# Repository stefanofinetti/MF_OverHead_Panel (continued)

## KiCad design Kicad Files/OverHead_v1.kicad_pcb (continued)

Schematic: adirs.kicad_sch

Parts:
H21, H22, H23, H24: MountingHole; MountingHole_3.2mm_M3_DIN965_Pad_TopBottom
SW24: GND_CTL; G-Switch PS-7054DVB-6PN
SW25: ADR_1; Rotary_SW_8x1
SW26: ADR_2; Rotary_SW_8x1
SW27: ADR_3; Rotary_SW_8x1

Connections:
ADR_1_ATT: SW25.3; also elsewhere on the board
ADR_1_NAV: SW25.2; also elsewhere on the board
ADR_1_OFF: SW25.1; also elsewhere on the board
ADR_2_ATT: SW26.3; also elsewhere on the board
ADR_2_NAV: SW26.2; also elsewhere on the board
ADR_2_OFF: SW26.1; also elsewhere on the board
ADR_3_ATT: SW27.3; also elsewhere on the board
ADR_3_NAV: SW27.2; also elsewhere on the board
ADR_3_OFF: SW27.1; also elsewhere on the board
GND: SW24.2, SW25.9, SW26.9, SW27.9; also elsewhere on the board
GND_CTL_SW: SW24.1; also elsewhere on the board

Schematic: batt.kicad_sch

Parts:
H30, H31, H32, H33: MountingHole; MountingHole_3.2mm_M3_DIN965_Pad_TopBottom
SW14: OXY_CREW_SUPPLY; G-Switch PS-7054DVB-6PN
SW15: ELEC_BATT_1; G-Switch PS-7054DVB-6PN
SW16: ELEC_BATT_2; G-Switch PS-7054DVB-6PN

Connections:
ELEC_BATT_1_SW: SW15.1; also elsewhere on the board
ELEC_BATT_2_SW: SW16.1; also elsewhere on the board
GND: SW14.2, SW15.2, SW16.2; also elsewhere on the board
OXY_CREW_SUPPLY_SW: SW14.1; also elsewhere on the board

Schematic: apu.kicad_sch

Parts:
H1, H2, H3, H4: MountingHole; MountingHole_3.2mm_M3_DIN965_Pad_TopBottom
SW1: APU_MASTER_SW; G-Switch PS-7054DVB-6PN
SW2: APU_START_SW; G-Switch PS-7054DVB-6PN

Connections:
APU_MASTER_SW: SW1.1; also elsewhere on the board
APU_START_SW: SW2.1; also elsewhere on the board
GND: SW1.2, SW2.2; also elsewhere on the board

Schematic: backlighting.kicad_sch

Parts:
D5, D6, D7, D8, D9, D10, D11, D12, D13, D14, D15, D16, D17, D18, D19, D20, D21, D22, D23, D24, D25, D26, D27, D28, D29, D30, D31, D32, D33, D34, D35, D36, D37, D38, D39, D40, D41, D42, D43, D44, D45, D46, D47, D48, D49, D53, D54, D55, D56, D57, D58, D59, D60, D61, D62, D63, D64, D65, D66, D67, D68, D69, D70, D71, D72, D73, D74, D81, D82, D83, D84, D85, D86, D88, D93, D94, D95, D96, D97, D98, D100, D101, D102, D104, D105, D110, D111, D112, D113, D114, D115, D116, D117, D118, D119, D134, D135, D136, D137, D138, D139, D140, D141, D142, D143, D144, D146, D147, D148, D149, D150, D151, D152, D153, D154, D155, D156, D157, D158, D159, D160, D161: LED; LED_1206_3216Metric_Pad1.42x1.75mm_HandSolder
R9, R10, R11, R12, R13, R14, R15, R16, R17, R18, R19, R20, R21, R22, R23, R24, R25, R26, R27, R28, R29, R30, R31, R32, R33, R34, R35, R36, R37, R38, R39, R40, R57, R58, R59, R60, R61, R62, R63, R64, R65, R66, R67, R68, R69, R70, R71, R72, R73, R74, R75, R76, R77, R78, R79, R80, R81, R82, R83, R84, R85: 150; R_1206_3216Metric_Pad1.30x1.75mm_HandSolder

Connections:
+9V: D5.2 (A), D7.2 (A), D9.2 (A), D11.2 (A), D13.2 (A), D15.2 (A), D17.2 (A), D19.2 (A), D21.2 (A), D23.2 (A), D25.2 (A), D27.2 (A), D29.2 (A), D31.2 (A), D33.2 (A), D35.2 (A), D37.2 (A), D39.2 (A), D41.2 (A), D43.2 (A), D45.2 (A), D47.2 (A), D49.2 (A), D54.2 (A), D56.2 (A), D58.2 (A), D60.2 (A), D62.2 (A), D64.2 (A), D66.2 (A), D68.2 (A), D70.2 (A), D72.2 (A), D74.2 (A), D82.2 (A), D84.2 (A), D86.2 (A), D93.2 (A), D95.2 (A), D97.2 (A), D100.2 (A), D102.2 (A), D105.2 (A), D111.2 (A), D113.2 (A), D115.2 (A), D117.2 (A), D119.2 (A), D135.2 (A), D137.2 (A), D139.2 (A), D141.2 (A), D143.2 (A), D146.2 (A), D148.2 (A), D150.2 (A), D152.2 (A), D154.2 (A), D156.2 (A), D158.2 (A), D160.2 (A); also elsewhere on the board
GND: R9.2, R10.2, R11.2, R12.2, R13.2, R14.2, R15.2, R16.2, R17.2, R18.2, R19.2, R20.2, R21.2, R22.2, R23.2, R24.2, R25.2, R26.2, R27.2, R28.2, R29.2, R30.2, R31.2, R32.2, R33.2, R34.2, R35.2, R36.2, R37.2, R38.2, R39.2, R40.2, R57.2, R58.2, R59.2, R60.2, R61.2, R62.2, R63.2, R64.2, R65.2, R66.2, R67.2, R68.2, R69.2, R70.2, R71.2, R72.2, R73.2, R74.2, R75.2, R76.2, R77.2, R78.2, R79.2, R80.2, R81.2, R82.2, R83.2, R84.2, R85.2; also elsewhere on the board
unnamed: D5.1 (K), D6.2 (A)
unnamed: D6.1 (K), R9.1
unnamed: D7.1 (K), D8.2 (A)
unnamed: D8.1 (K), R10.1
unnamed: D9.1 (K), D10.2 (A)
unnamed: D10.1 (K), R11.1
unnamed: D11.1 (K), D12.2 (A)
unnamed: D12.1 (K), R12.1
unnamed: D13.1 (K), D14.2 (A)
unnamed: D14.1 (K), R13.1
unnamed: D15.1 (K), D16.2 (A)
unnamed: D16.1 (K), R14.1
unnamed: D17.1 (K), D18.2 (A)
unnamed: D18.1 (K), R15.1
unnamed: D19.1 (K), D20.2 (A)
unnamed: D20.1 (K), R16.1
unnamed: D21.1 (K), D22.2 (A)
unnamed: D22.1 (K), R17.1
unnamed: D23.1 (K), D24.2 (A)
unnamed: D24.1 (K), R18.1
unnamed: D25.1 (K), D26.2 (A)
unnamed: D26.1 (K), R19.1
unnamed: D27.1 (K), D28.2 (A)
unnamed: D28.1 (K), R20.1
unnamed: D29.1 (K), D30.2 (A)
unnamed: D30.1 (K), R21.1
unnamed: D31.1 (K), D32.2 (A)
unnamed: D32.1 (K), R22.1
unnamed: D33.1 (K), D34.2 (A)
unnamed: D34.1 (K), R23.1
unnamed: D35.1 (K), D36.2 (A)
unnamed: D36.1 (K), R24.1
unnamed: D37.1 (K), D38.2 (A)
unnamed: D38.1 (K), R25.1
unnamed: D39.1 (K), D40.2 (A)
unnamed: D40.1 (K), R26.1
unnamed: D41.1 (K), D42.2 (A)
unnamed: D42.1 (K), R27.1
unnamed: D43.1 (K), D44.2 (A)
unnamed: D44.1 (K), R28.1
unnamed: D45.1 (K), D46.2 (A)
unnamed: D46.1 (K), R29.1
unnamed: D47.1 (K), D48.2 (A)
unnamed: D48.1 (K), R30.1
unnamed: D49.1 (K), D53.2 (A)
unnamed: D53.1 (K), R31.1
unnamed: D54.1 (K), D55.2 (A)
unnamed: D55.1 (K), R32.1
unnamed: D56.1 (K), D57.2 (A)
unnamed: D57.1 (K), R33.1
unnamed: D58.1 (K), D59.2 (A)
unnamed: D59.1 (K), R34.1
unnamed: D60.1 (K), D61.2 (A)
unnamed: D61.1 (K), R35.1
unnamed: D62.1 (K), D63.2 (A)
unnamed: D63.1 (K), R36.1
unnamed: D64.1 (K), D65.2 (A)
unnamed: D65.1 (K), R37.1
unnamed: D66.1 (K), D67.2 (A)
unnamed: D67.1 (K), R38.1
unnamed: D68.1 (K), D69.2 (A)
unnamed: D69.1 (K), R39.1
unnamed: D70.1 (K), D71.2 (A)
unnamed: D71.1 (K), R40.1
unnamed: D72.1 (K), D73.2 (A)
unnamed: D73.1 (K), R57.1
unnamed: D74.1 (K), D81.2 (A)
unnamed: D81.1 (K), R58.1
unnamed: D82.1 (K), D83.2 (A)
unnamed: D83.1 (K), R59.1
unnamed: D84.1 (K), D85.2 (A)
unnamed: D85.1 (K), R60.1
unnamed: D86.1 (K), D88.2 (A)
unnamed: D88.1 (K), R61.1
unnamed: D93.1 (K), D94.2 (A)
unnamed: D94.1 (K), R62.1
unnamed: D95.1 (K), D96.2 (A)
unnamed: D96.1 (K), R63.1
unnamed: D97.1 (K), D98.2 (A)
unnamed: D98.1 (K), R64.1
unnamed: D100.1 (K), D101.2 (A)
unnamed: D101.1 (K), R65.1
unnamed: D102.1 (K), D104.2 (A)
unnamed: D104.1 (K), R66.1
unnamed: D105.1 (K), D110.2 (A)
unnamed: D110.1 (K), R67.1
unnamed: D111.1 (K), D112.2 (A)
unnamed: D112.1 (K), R68.1
unnamed: D113.1 (K), D114.2 (A)
unnamed: D114.1 (K), R69.1
unnamed: D115.1 (K), D116.2 (A)
unnamed: D116.1 (K), R70.1
unnamed: D117.1 (K), D118.2 (A)
unnamed: D118.1 (K), R71.1
unnamed: D119.1 (K), D134.2 (A)
unnamed: D134.1 (K), R72.1
unnamed: D135.1 (K), D136.2 (A)
unnamed: D136.1 (K), R73.1
unnamed: D137.1 (K), D138.2 (A)
unnamed: D138.1 (K), R74.1
unnamed: D139.1 (K), D140.2 (A)
unnamed: D140.1 (K), R75.1
unnamed: D141.1 (K), D142.2 (A)
unnamed: D142.1 (K), R76.1
unnamed: D143.1 (K), D144.2 (A)
unnamed: D144.1 (K), R77.1
unnamed: D146.1 (K), D147.2 (A)
unnamed: D147.1 (K), R78.1
unnamed: D148.1 (K), D149.2 (A)
unnamed: D149.1 (K), R79.1
unnamed: D150.1 (K), D151.2 (A)
unnamed: D151.1 (K), R80.1
unnamed: D152.1 (K), D153.2 (A)
unnamed: D153.1 (K), R81.1
unnamed: D154.1 (K), D155.2 (A)
unnamed: D155.1 (K), R82.1
unnamed: D156.1 (K), D157.2 (A)
unnamed: D157.1 (K), R83.1
unnamed: D158.1 (K), D159.2 (A)
unnamed: D159.1 (K), R84.1
unnamed: D160.1 (K), D161.2 (A)
unnamed: D161.1 (K), R85.1

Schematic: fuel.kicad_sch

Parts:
H25, H26, H27, H28, H29: MountingHole; MountingHole_3.2mm_M3_DIN965_Pad_TopBottom
SW17: LT_TK_PUMP_1; G-Switch PS-7054DVB-6PN
SW18: LT_TK_PUMP_2; G-Switch PS-7054DVB-6PN
SW19: L_XFER; G-Switch PS-7054DVB-6PN
SW20: X_FEED; G-Switch PS-7054DVB-6PN
SW21: R_XFER; G-Switch PS-7054DVB-6PN
SW22: RT_TK_PUMP_1; G-Switch PS-7054DVB-6PN
SW23: RT_TK_PUMP_2; G-Switch PS-7054DVB-6PN

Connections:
CTR_TK_PUMP_1_SW: SW19.1; also elsewhere on the board
CTR_TK_PUMP_2_SW: SW21.1; also elsewhere on the board
GND: SW17.2, SW18.2, SW19.2, SW20.2, SW21.2, SW22.2, SW23.2; also elsewhere on the board
LT_TK_PUMP_1_SW: SW17.1; also elsewhere on the board
LT_TK_PUMP_2_SW: SW18.1; also elsewhere on the board
RT_TK_PUMP_1_SW: SW22.1; also elsewhere on the board
RT_TK_PUMP_2_SW: SW23.1; also elsewhere on the board
XFEED_SW: SW20.1; also elsewhere on the board

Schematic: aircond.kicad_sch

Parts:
H17, H18, H19, H20: MountingHole; MountingHole_3.2mm_M3_DIN965_Pad_TopBottom
SW10: APU BLEED; G-Switch PS-7054DVB-6PN
SW11: PACK1; G-Switch PS-7054DVB-6PN
SW12: PACK2; G-Switch PS-7054DVB-6PN
SW13: EXT_PWR; G-Switch PS-7054DVB-6PN

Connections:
APU_BLEED_SW: SW10.1; also elsewhere on the board
EXT_PWR_SW: SW13.1; also elsewhere on the board
GND: SW10.2, SW11.2, SW12.2, SW13.2; also elsewhere on the board
PACK1_SW: SW11.1; also elsewhere on the board
PACK2_SW: SW12.1; also elsewhere on the board

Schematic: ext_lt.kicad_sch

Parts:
H5, H6, H7, H8: MountingHole; MountingHole_3.2mm_M3_DIN965_Pad_TopBottom
S1: LDG_LIGHT_L; Toggle_Switch_100SP1T1B4M2QE; MPN 100SP1T1B4M2QE; Digi-Key_PN EG2355-ND
S2: LDG_LIGHT_R; Toggle_Switch_100SP1T1B4M2QE; MPN 100SP1T1B4M2QE; Digi-Key_PN EG2355-ND
S3: NOSE_LIGHT; Toggle_Switch_100SP1T1B4M2QE; MPN 100SP1T1B4M2QE; Digi-Key_PN EG2355-ND
S4: NAV&LOGO; Toggle_Switch_100SP1T1B4M2QE; MPN 100SP1T1B4M2QE; Digi-Key_PN EG2355-ND
S5: WING; Toggle_Switch_100SP1T1B4M2QE; MPN 100SP1T1B4M2QE; Digi-Key_PN EG2355-ND
S6: BEACON; Toggle_Switch_100SP1T1B4M2QE; MPN 100SP1T1B4M2QE; Digi-Key_PN EG2355-ND
S7: STROBE; Toggle_Switch_100SP1T1B4M2QE; MPN 100SP1T1B4M2QE; Digi-Key_PN EG2355-ND
S8: RWY TURN; Toggle_Switch_100SP1T1B4M2QE; MPN 100SP1T1B4M2QE; Digi-Key_PN EG2355-ND

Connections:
BEACON_ON: S6.1; also elsewhere on the board
GND: S1.2 (Com), S2.2 (Com), S3.2 (Com), S4.2 (Com), S5.2 (Com), S6.2 (Com), S7.2 (Com), S8.2 (Com); also elsewhere on the board
L_LDG_LIGHT_ON: S1.1; also elsewhere on the board
L_LDG_LIGHT_RETR: S1.3; also elsewhere on the board
NAV_1: S4.1; also elsewhere on the board
NAV_1_OFF: S4.3; also elsewhere on the board
NOSE_OFF: S3.3; also elsewhere on the board
NOSE_TO: S3.1; also elsewhere on the board
RWY_TURN_ON: S8.1; also elsewhere on the board
R_LDG_LIGHT_ON: S2.1; also elsewhere on the board
R_LDG_LIGHT_RETR: S2.3; also elsewhere on the board
STROBE_ON: S7.1; also elsewhere on the board
WING_ON: S5.1; also elsewhere on the board

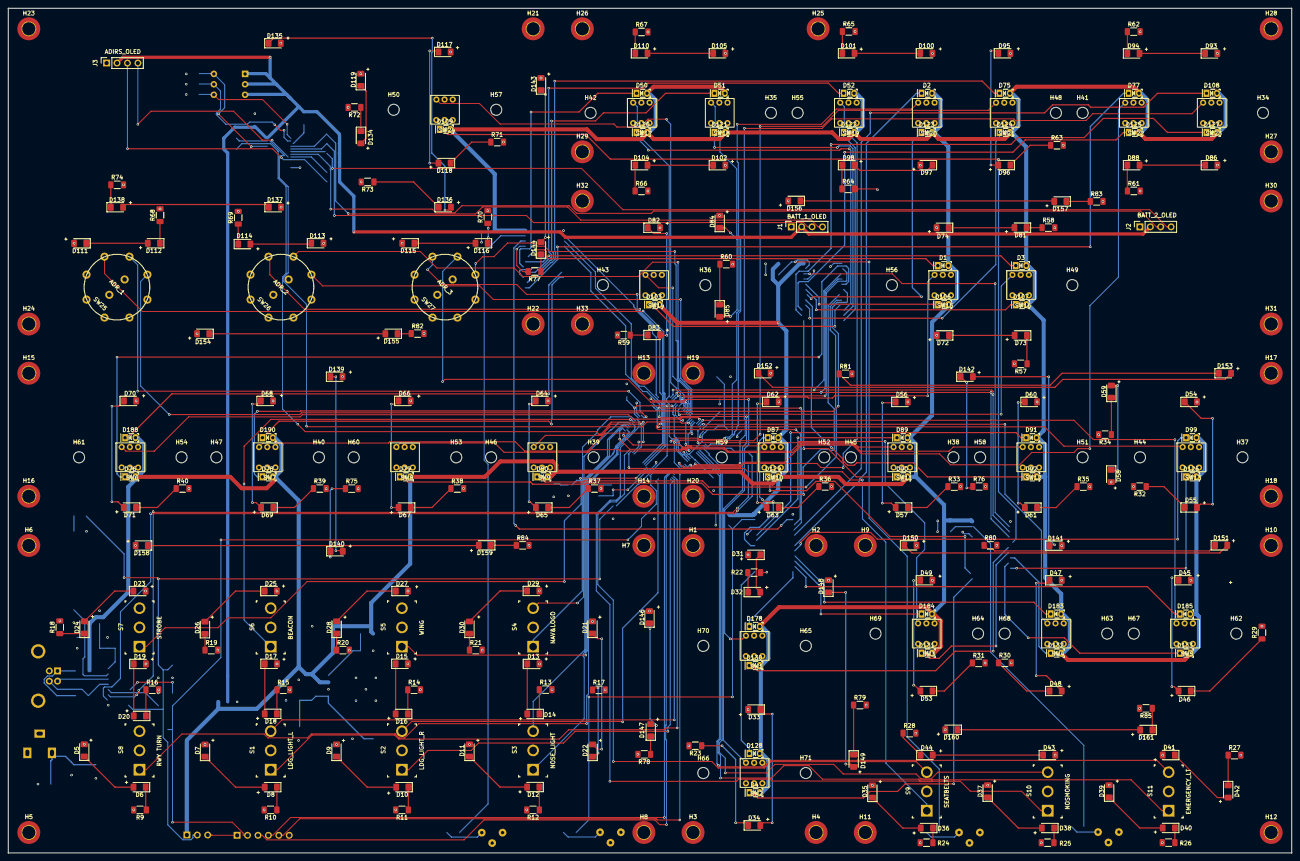
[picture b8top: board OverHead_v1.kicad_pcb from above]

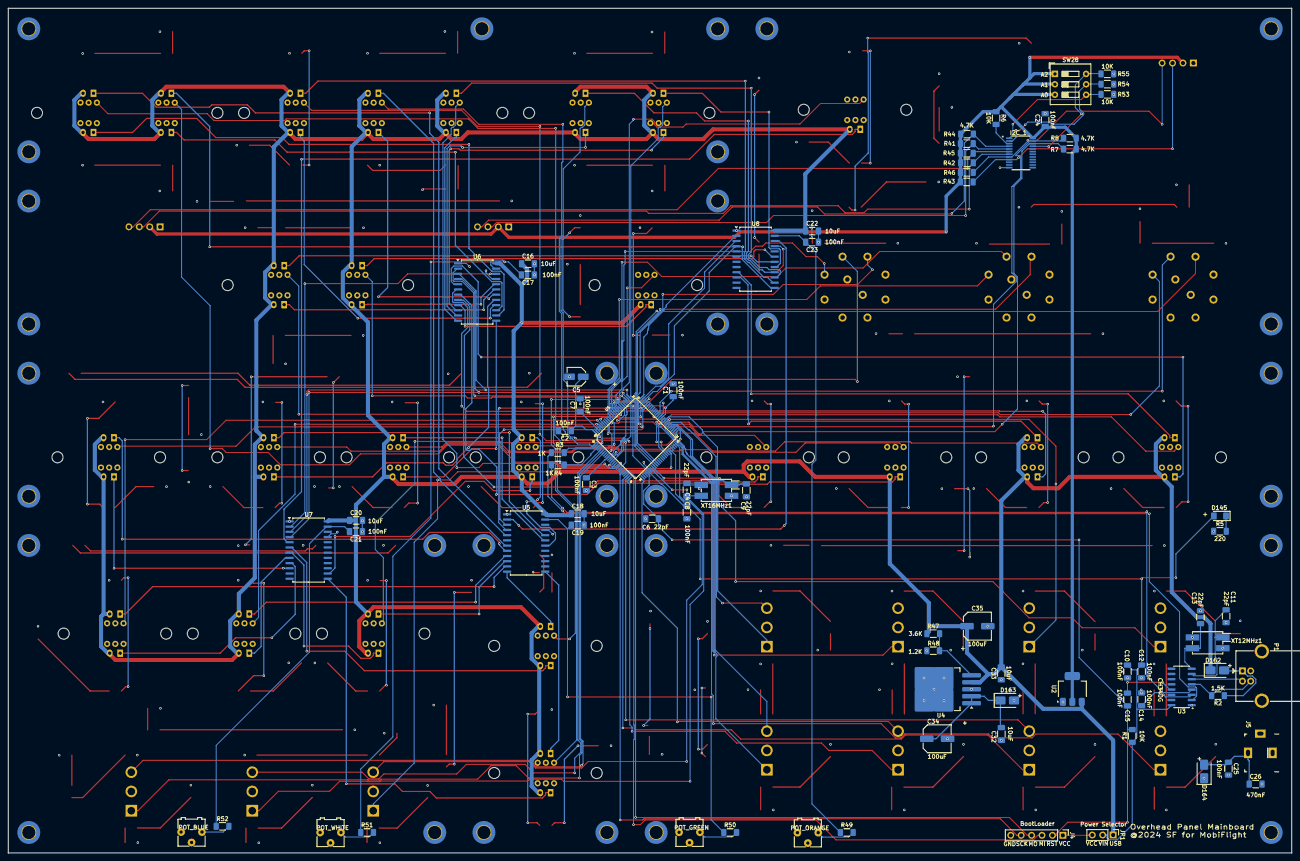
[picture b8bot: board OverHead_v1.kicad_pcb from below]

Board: 4 copper layers, 313.0 x 206.0 mm, 416 parts (77 on the bottom side), 271 nets.

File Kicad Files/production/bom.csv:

Designator,Footprint,Quantity,Value,LCSC Part #
"C1, C10, C12, C14, C15, C17, C19, C2, C21, C23, C24, C25, C3, C4, C7",1206,15,100nF,
"C11, C13, C6, C8, C9",1206,5,22pF,
"C16, C18, C20, C22, C32, C33",1206,6,10uF,
C26,1206,1,470nF,
"C34, C35",C_Elec_6.3x7.7,2,100uF,
C5,C_Elec_4x5.4,1,10uF,
"D1, D120, D121, D122, D123, D124, D125, D127, D129, D130, D131, D183, D185, D3, D4, D76, D79, D91",LED_Rectangular_W3.9mm_H1.8mm_FlatTop,18,STS,
"D10, D100, D101, D102, D104, D105, D11, D110, D111, D112, D113, D114, D115, D116, D117, D118, D119, D12, D13, D134, D135, D136, D137, D138, D139, D14, D140, D141, D142, D143, D144, D145, D146, D147, D148, D149, D15, D150, D151, D152, D153, D154, D155, D156, D157, D158, D159, D16, D160, D161, D17, D18, D19, D20, D21, D22, D23, D24, D25, D26, D27, D28, D29, D30, D31, D32, D33, D34, D35, D36, D37, D38, D39, D40, D41, D42, D43, D44, D45, D46, D47, D48, D49, D5, D53, D54, D55, D56, D57, D58, D59, D6, D60, D61, D62, D63, D64, D65, D66, D67, D68, D69, D7, D70, D71, D72, D73, D74, D8, D81, D82, D83, D84, D85, D86, D88, D9, D93, D94, D95, D96, D97, D98",1206,123,LED,
"D103, D106, D107, D108, D109, D126, D128, D132, D133, D178, D184, D188, D190, D2, D50, D51, D52, D75, D77, D78, D80, D87, D89, D90, D92, D99",LED_Rectangular_W3.9mm_H1.8mm_FlatTop,26,ANN,
D162,D_SMA_DO-214-AC,1,USB_Protection,
D163,D_SMA_DO-214-AC,1,BarrelJack_Prot,
D164,D_SMA_DO-214-AC,1,BarrelJackProt_FromLed,
I2C_1,SOP65P640X120-24N,1,PCA9548APW,
J1,PinSocket_1x04_P2.54mm_Vertical,1,BATT_1_OLED,
J2,PinSocket_1x04_P2.54mm_Vertical,1,BATT_2_OLED,
J3,PinSocket_1x04_P2.54mm_Vertical,1,ADIRS_OLED,
J4,PinHeader_1x06_P2.54mm_Vertical,1,BootLoader,
J5,Barrel_Jack_5.5mmODx2.1mmID_PJ-102A,1,PJ-102A,PJ-102A
JP1,PinHeader_1x03_P2.54mm_Vertical,1,Power Selector,
P1,USB_B_OST_USB-B1HSxx_Horizontal,1,USB_C_Plug_USB2.0,
"R1, R53, R54, R55, R6",1206,5,10K,
"R10, R11, R12, R13, R14, R15, R16, R17, R18, R19, R20, R21, R22, R23, R24, R25, R26, R27, R28, R29, R30, R31, R32, R33, R34, R35, R36, R37, R38, R39, R40, R57, R58, R59, R60, R61, R62, R63, R64, R65, R66, R67, R68, R69, R70, R71, R72, R73, R74, R75, R76, R77, R78, R79, R80, R81, R82, R83, R84, R85, R9",1206,61,150,
R2,1206,1,1.5K,
"R3, R4",1206,2,1K,
"R41, R42, R43, R44, R45, R46, R7, R8",1206,8,4.7K,
R47,1206,1,3.6K,
R48,1206,1,1.2K,
"R49, R50, R51, R52",1206,4,56,
R5,1206,1,220,
RV1,potentiometer_3362P,1,POT_WHITE,
RV2,potentiometer_3362P,1,POT_GREEN,
RV3,potentiometer_3362P,1,POT_BLUE,
RV4,potentiometer_3362P,1,POT_ORANGE,
S1,Toggle_Switch_100SP1T1B4M2QE,1,LDG_LIGHT_L,100SP1T1B4M2QE
S10,Toggle_Switch_100SP1T1B4M2QE,1,NOSMOKING,100SP1T1B4M2QE
S11,Toggle_Switch_100SP1T1B4M2QE,1,EMERGENCY_LT,100SP1T1B4M2QE
S2,Toggle_Switch_100SP1T1B4M2QE,1,LDG_LIGHT_R,100SP1T1B4M2QE
S3,Toggle_Switch_100SP1T1B4M2QE,1,NOSE_LIGHT,100SP1T1B4M2QE
S4,Toggle_Switch_100SP1T1B4M2QE,1,NAV&LOGO,100SP1T1B4M2QE
S5,Toggle_Switch_100SP1T1B4M2QE,1,WING,100SP1T1B4M2QE
S6,Toggle_Switch_100SP1T1B4M2QE,1,BEACON,100SP1T1B4M2QE
S7,Toggle_Switch_100SP1T1B4M2QE,1,STROBE,100SP1T1B4M2QE
S8,Toggle_Switch_100SP1T1B4M2QE,1,RWY TURN,100SP1T1B4M2QE
S9,Toggle_Switch_100SP1T1B4M2QE,1,SEATBELTS,100SP1T1B4M2QE
SW1,G-Switch PS-7054DVB-6PN,1,APU_MASTER_SW,
SW10,G-Switch PS-7054DVB-6PN,1,APU BLEED,
SW11,G-Switch PS-7054DVB-6PN,1,PACK1,
SW12,G-Switch PS-7054DVB-6PN,1,PACK2,
SW13,G-Switch PS-7054DVB-6PN,1,EXT_PWR,
SW14,G-Switch PS-7054DVB-6PN,1,OXY_CREW_SUPPLY,
SW15,G-Switch PS-7054DVB-6PN,1,ELEC_BATT_1,
SW16,G-Switch PS-7054DVB-6PN,1,ELEC_BATT_2,
SW17,G-Switch PS-7054DVB-6PN,1,LT_TK_PUMP_1,
SW18,G-Switch PS-7054DVB-6PN,1,LT_TK_PUMP_2,
SW19,G-Switch PS-7054DVB-6PN,1,L_XFER,
SW2,G-Switch PS-7054DVB-6PN,1,APU_START_SW,
SW20,G-Switch PS-7054DVB-6PN,1,X_FEED,
SW21,G-Switch PS-7054DVB-6PN,1,R_XFER,
SW22,G-Switch PS-7054DVB-6PN,1,RT_TK_PUMP_1,
SW23,G-Switch PS-7054DVB-6PN,1,RT_TK_PUMP_2,
SW24,G-Switch PS-7054DVB-6PN,1,GND_CTL,
SW25,Rotary_SW_8x1,1,ADR_1,
SW26,Rotary_SW_8x1,1,ADR_2,
SW27,Rotary_SW_8x1,1,ADR_3,
SW28,SW_DIP_SPSTx03_Slide_9.78x9.8mm_W7.62mm_P2.54mm,1,SW_DIP_x03,
SW3,G-Switch PS-7054DVB-6PN,1,ANTI_ICE_WING_SW,
SW4,G-Switch PS-7054DVB-6PN,1,ANTI_ICE_ENG1_SW,
SW5,G-Switch PS-7054DVB-6PN,1,ANTI_ICE_ENG2_SW,
SW6,G-Switch PS-7054DVB-6PN,1,TERR,
SW7,G-Switch PS-7054DVB-6PN,1,SYS,
SW8,G-Switch PS-7054DVB-6PN,1,G/S MODE,
SW9,G-Switch PS-7054DVB-6PN,1,LDG FLAPS 3,
U1,TQFP100-0.5-14X14MM,1,ATMega2560,
U2,SOT-223-3_TabPin2,1,AMS1117-3.3,
U3,SOIC-16_3.9x9.9mm_P1.27mm,1,CH340G,
U4,TO-263-5_TabPin3,1,MIC29302WU,
U5,SOP-24_7.5x15.4mm_P1.27mm,1,DM13A-GREEN-0-100,
U6,SOP-24_7.5x15.4mm_P1.27mm,1,DM13A-WHITE-0-100,
U7,SOP-24_7.5x15.4mm_P1.27mm,1,DM13A-BLUE-0-100,
U8,SOP-24_7.5x15.4mm_P1.27mm,1,DM13A-ORANGE-0-100,
XT12MHZ1,Crystal_SMD_EuroQuartz_MQ-4Pin_7.0x5.0mm_HandSoldering,1,12MHz,
XT16MHZ1,Crystal_SMD_EuroQuartz_MQ-4Pin_7.0x5.0mm_HandSoldering,1,16MHz,

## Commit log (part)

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2024-12-02 First commit of OverHead Panel
2024-12-02 Added GPL License
2024-12-02 Added Readme file
2024-12-03 Added Bambu Project for the complete OverHead (incomplete yet)
2025-01-14 VsCode firmware file + changes in the PCB layout
2025-01-14 Some fixes on the json devices file
2025-01-15 Fixed some issues with the code and path on remote drive
2025-01-15 Edited PCB Layout. Added 56 ohm resistor to 0-100ohm trimpots for better dimming management; Changed 16 and 12 Mhz crystals footprint to accomodate better ones (7x5mm hand soldering pads). Various En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
2025-01-15 Changed the polarity label for some backlighting led that were wrongly placed
2025-01-15 Modified the 8x1 rotary switch pin position to reflect the ones I bought. Had to move each pin 1 place on its right basically rotating the entire switch by 45°
2025-01-15 Improved pcb design by adding a dip-switch to alter I2C physical address and other small design improvements
2025-06-21 New STL files for APU OVHD element, other coming in the next few weeks
